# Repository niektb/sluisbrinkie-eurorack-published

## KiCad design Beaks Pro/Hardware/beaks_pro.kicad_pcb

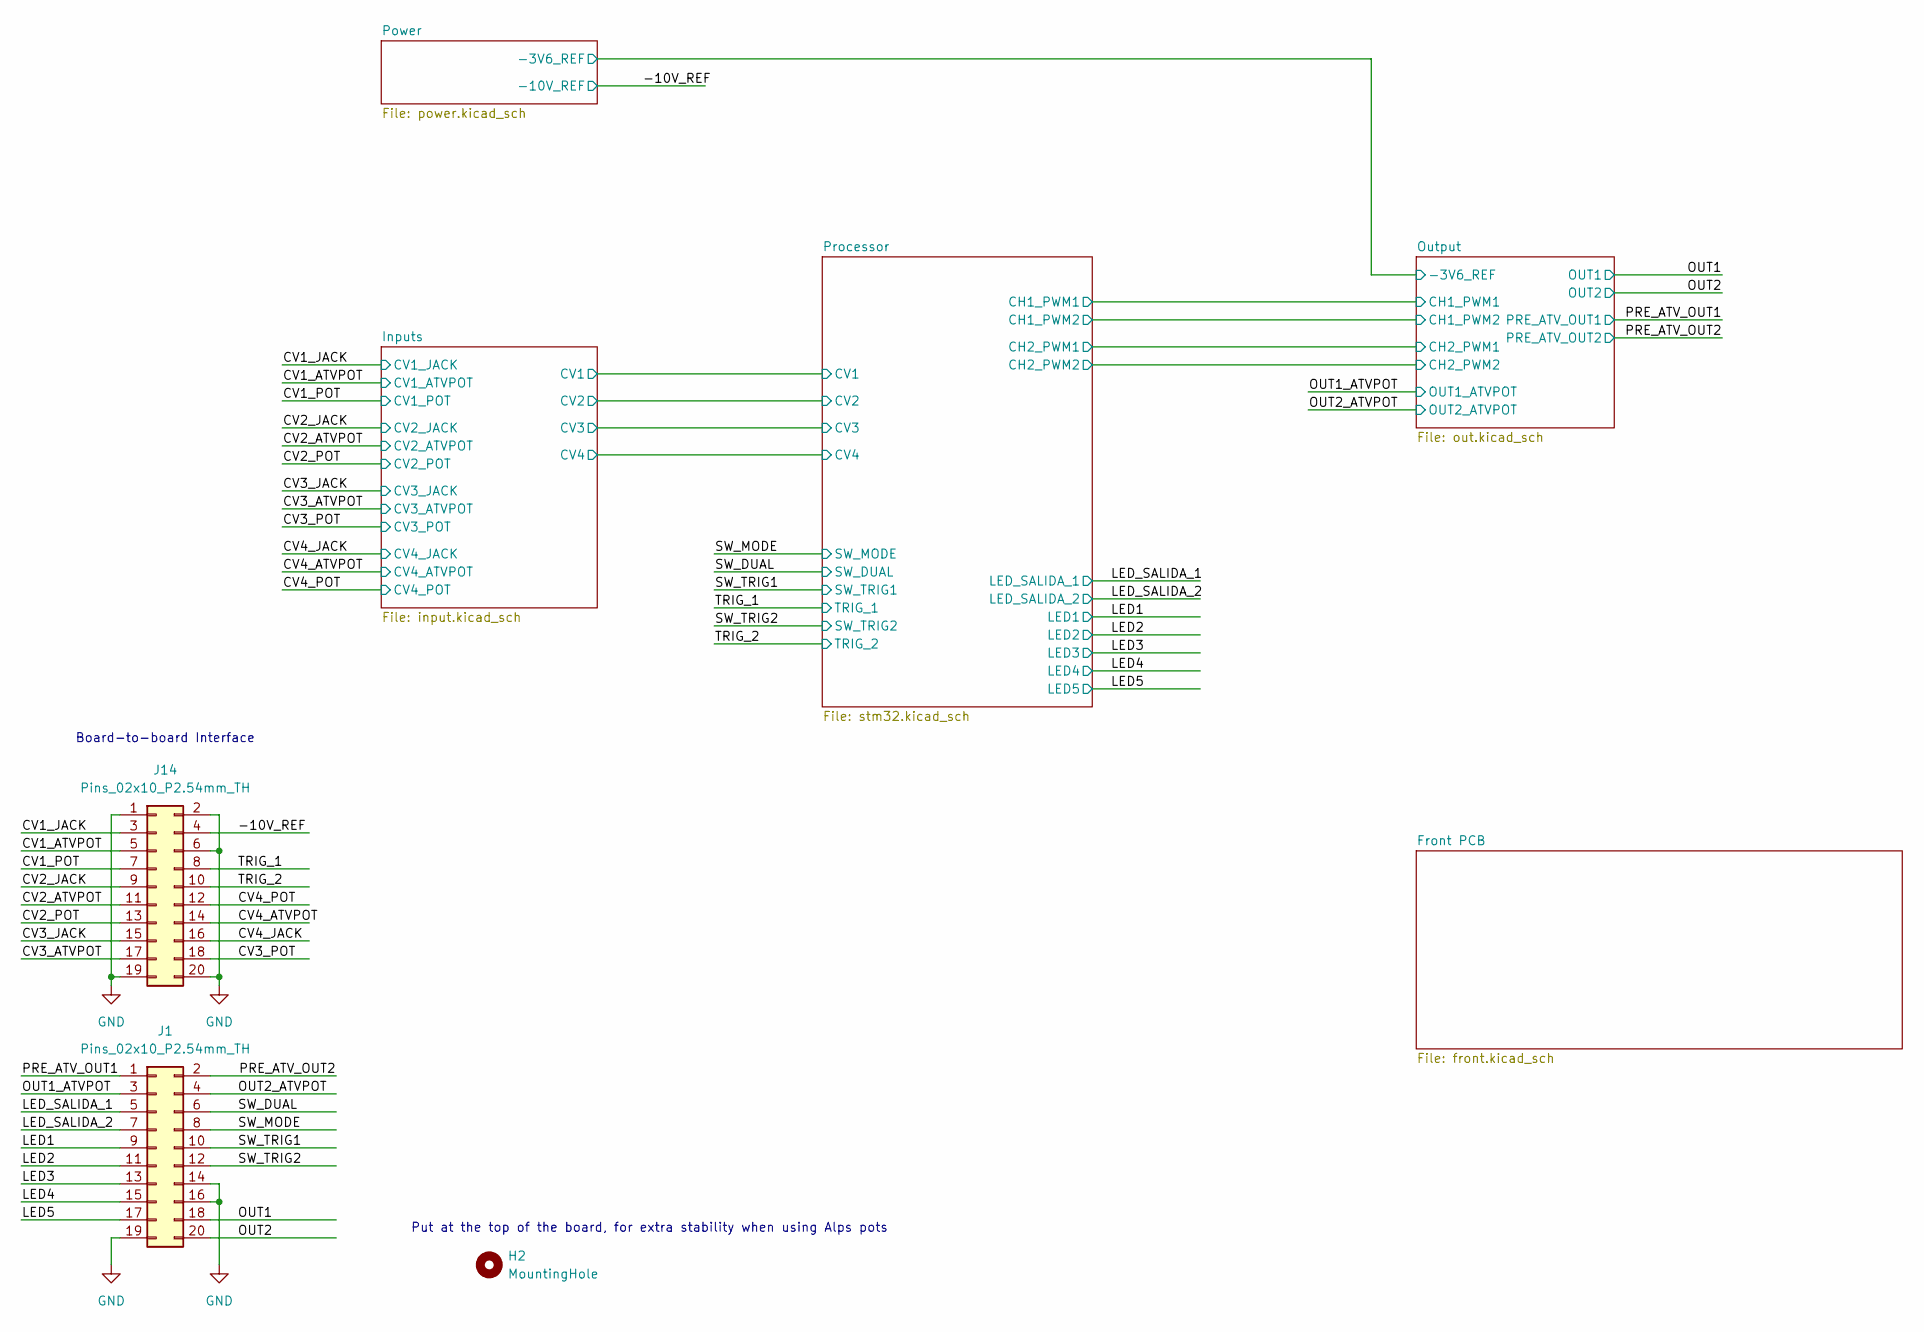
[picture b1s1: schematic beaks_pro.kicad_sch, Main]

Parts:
H2: MountingHole; MountingHole_2.7mm_M2.5
J1, J14: Pins_02x10_P2.54mm_TH; PinHeader_2x10_P2.54mm_Vertical

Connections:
/CV1_ATVPOT: J14.5; also elsewhere on the board
/CV1_JACK: J14.3; also elsewhere on the board
/CV1_POT: J14.7; also elsewhere on the board
/CV2_ATVPOT: J14.11; also elsewhere on the board
/CV2_JACK: J14.9; also elsewhere on the board
/CV2_POT: J14.13; also elsewhere on the board
/CV3_ATVPOT: J14.17; also elsewhere on the board
/CV3_JACK: J14.15; also elsewhere on the board
/CV3_POT: J14.18; also elsewhere on the board
/CV4_ATVPOT: J14.14; also elsewhere on the board
/CV4_JACK: J14.16; also elsewhere on the board
/CV4_POT: J14.12; also elsewhere on the board
/LED1: J1.9; also elsewhere on the board
/LED2: J1.11; also elsewhere on the board
/LED3: J1.13; also elsewhere on the board
/LED4: J1.15; also elsewhere on the board
/LED5: J1.17; also elsewhere on the board
/LED_SALIDA_1: J1.5; also elsewhere on the board
/LED_SALIDA_2: J1.7; also elsewhere on the board
/OUT1: J1.18; also elsewhere on the board
/OUT1_ATVPOT: J1.3; also elsewhere on the board
/OUT2: J1.20; also elsewhere on the board
/OUT2_ATVPOT: J1.4; also elsewhere on the board
/PRE_ATV_OUT1: J1.1; also elsewhere on the board
/PRE_ATV_OUT2: J1.2; also elsewhere on the board
/SW_DUAL: J1.6; also elsewhere on the board
/SW_MODE: J1.8; also elsewhere on the board
/SW_TRIG1: J1.10; also elsewhere on the board
/SW_TRIG2: J1.12; also elsewhere on the board
/TRIG_1: J14.8; also elsewhere on the board
/TRIG_2: J14.10; also elsewhere on the board

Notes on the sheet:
Put at the top of the board, for extra stability when using Alps pots
Board-to-board Interface

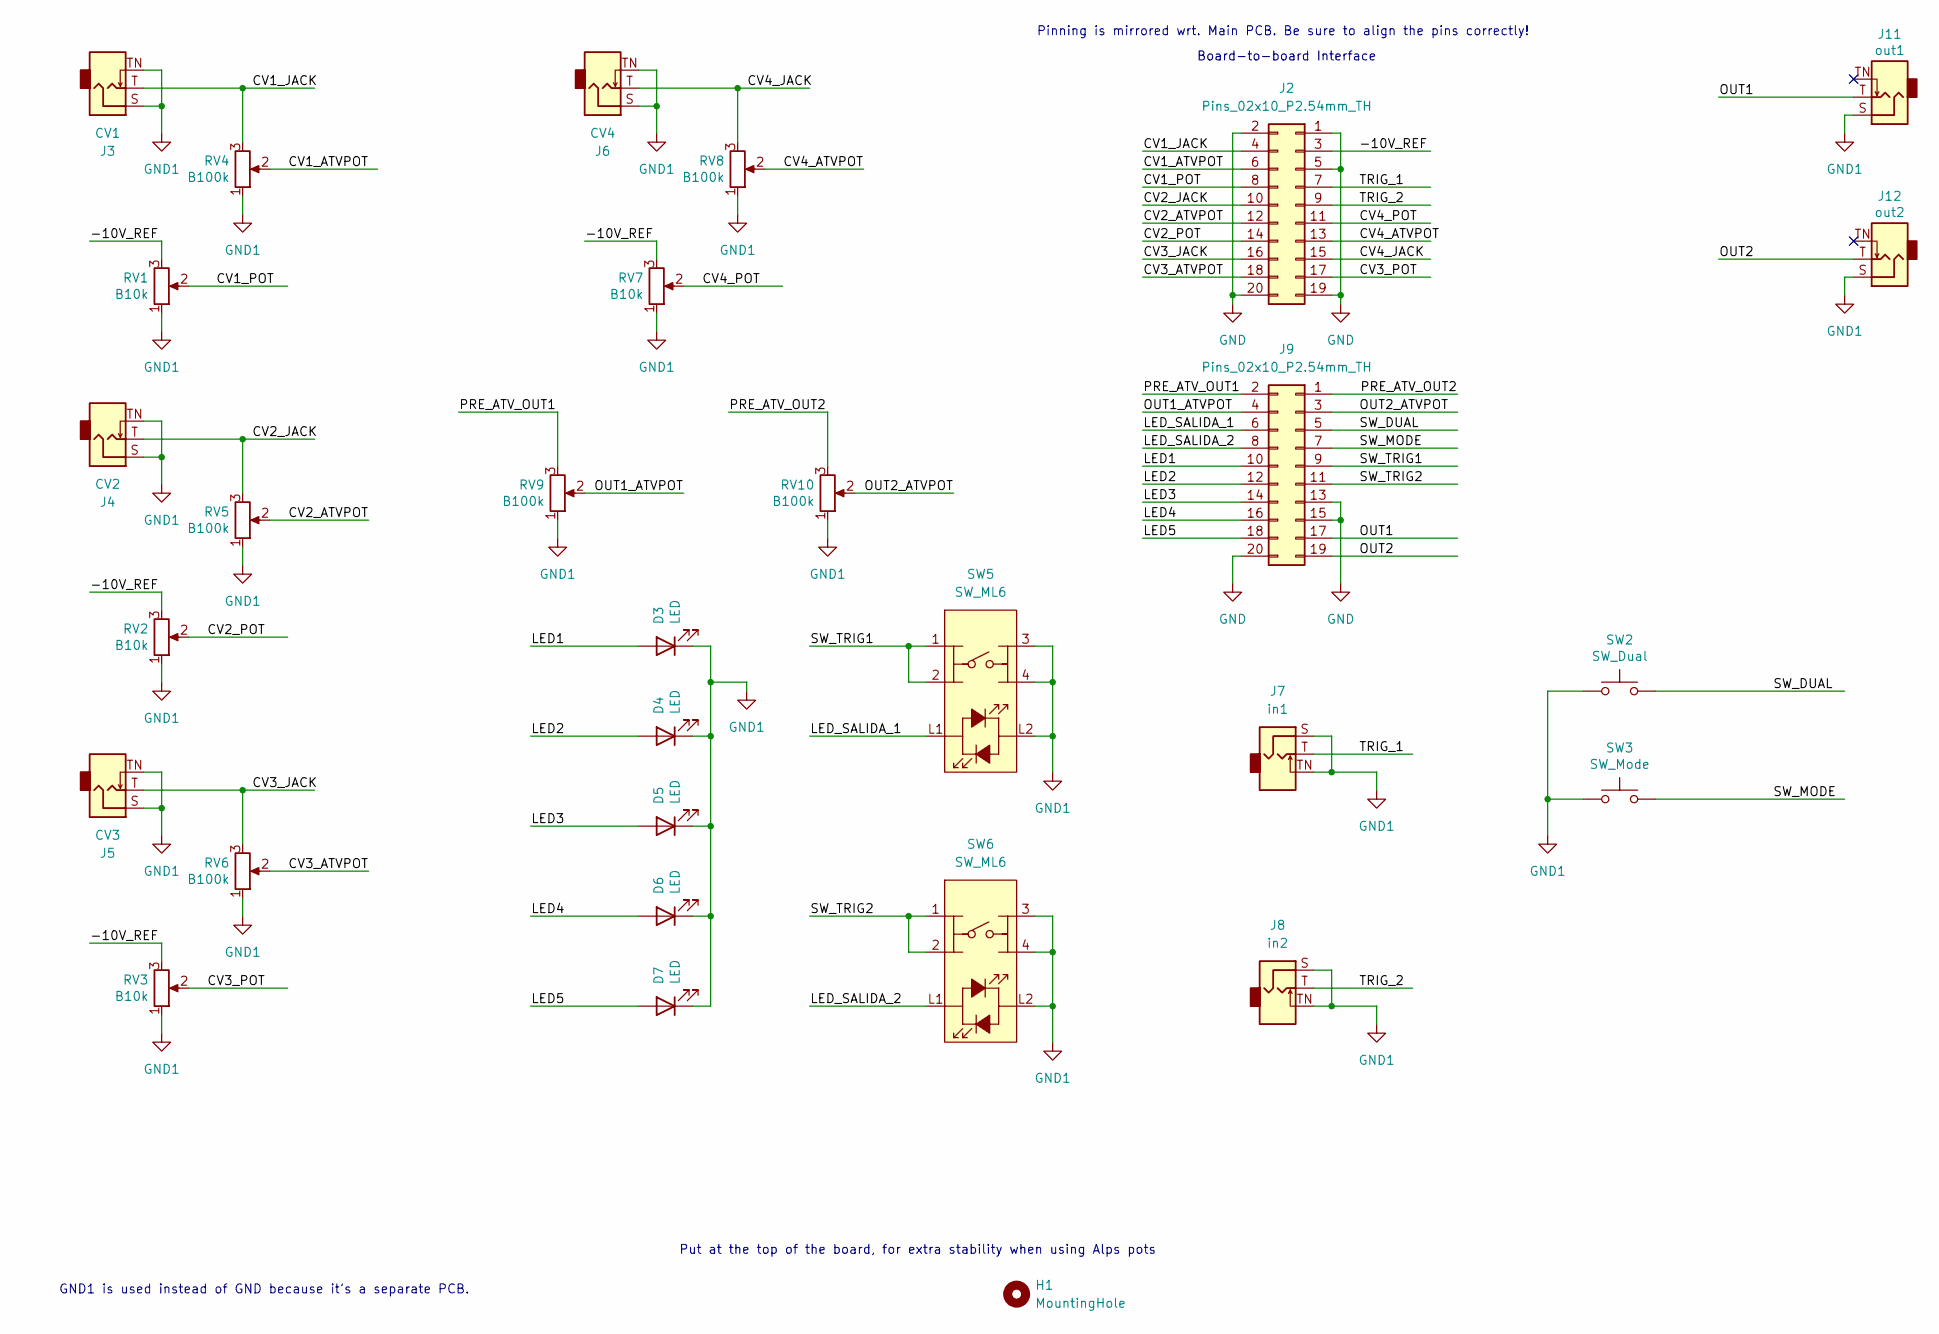
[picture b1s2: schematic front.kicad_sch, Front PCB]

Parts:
D3, D4, D5, D6, D7: LED; LED_D3.0mm
H1: MountingHole; MountingHole_2.7mm_M2.5
J2, J9: Pins_02x10_P2.54mm_TH; PinSocket_2x10_P2.54mm_Vertical
J3: CV1; Jack_3.5mm_QingPu_WQP-PJ398SM_Vertical_CircularHoles_3D
J4: CV2; Jack_3.5mm_QingPu_WQP-PJ398SM_Vertical_CircularHoles_3D
J5: CV3; Jack_3.5mm_QingPu_WQP-PJ398SM_Vertical_CircularHoles_3D
J6: CV4; Jack_3.5mm_QingPu_WQP-PJ398SM_Vertical_CircularHoles_3D
J7: in1; Jack_3.5mm_QingPu_WQP-PJ398SM_Vertical_CircularHoles_3D
J8: in2; Jack_3.5mm_QingPu_WQP-PJ398SM_Vertical_CircularHoles_3D
J11: out1; Jack_3.5mm_QingPu_WQP-PJ398SM_Vertical_CircularHoles_3D
J12: out2; Jack_3.5mm_QingPu_WQP-PJ398SM_Vertical_CircularHoles_3D
RV1, RV2, RV3, RV7: B10k; Potentiometer_Alps_RK09K_Single_Vertical_DSHAFT
RV4, RV5, RV6, RV8, RV9, RV10: B100k; Potentiometer_Alps_RK09K_Single_Vertical
SW2: SW_Dual; SW_PUSH_6mm_H13mm
SW3: SW_Mode; SW_PUSH_6mm_H13mm
SW5, SW6: SW_ML6; ML6-H2T2GQA

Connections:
/Front PCB/-10V_REF: J2.3, RV1.3, RV2.3, RV3.3, RV7.3
/Front PCB/CV1_ATVPOT: J2.6, RV4.2
/Front PCB/CV1_JACK: J2.4, J3.T, RV4.3
/Front PCB/CV1_POT: J2.8, RV1.2
/Front PCB/CV2_ATVPOT: J2.12, RV5.2
/Front PCB/CV2_JACK: J2.10, J4.T, RV5.3
/Front PCB/CV2_POT: J2.14, RV2.2
/Front PCB/CV3_ATVPOT: J2.18, RV6.2
/Front PCB/CV3_JACK: J2.16, J5.T, RV6.3
/Front PCB/CV3_POT: J2.17, RV3.2
/Front PCB/CV4_ATVPOT: J2.13, RV8.2
/Front PCB/CV4_JACK: J2.15, J6.T, RV8.3
/Front PCB/CV4_POT: J2.11, RV7.2
/Front PCB/LED1: D3.2 (A), J9.10
/Front PCB/LED2: D4.2 (A), J9.12
/Front PCB/LED3: D5.2 (A), J9.14
/Front PCB/LED4: D6.2 (A), J9.16
/Front PCB/LED5: D7.2 (A), J9.18
/Front PCB/LED_SALIDA_1: J9.6, SW5.L1
/Front PCB/LED_SALIDA_2: J9.8, SW6.L1
/Front PCB/OUT1: J9.17, J11.T
/Front PCB/OUT1_ATVPOT: J9.4, RV9.2
/Front PCB/OUT2: J9.19, J12.T
/Front PCB/OUT2_ATVPOT: J9.3, RV10.2
/Front PCB/PRE_ATV_OUT1: J9.2, RV9.3
/Front PCB/PRE_ATV_OUT2: J9.1, RV10.3
/Front PCB/SW_DUAL: J9.5, SW2.1
/Front PCB/SW_MODE: J9.7, SW3.1
/Front PCB/SW_TRIG1: J9.9, SW5.1, SW5.2
/Front PCB/SW_TRIG2: J9.11, SW6.1, SW6.2
/Front PCB/TRIG_1: J2.7, J7.T
/Front PCB/TRIG_2: J2.9, J8.T
GND1: D3.1 (K), D4.1 (K), D5.1 (K), D6.1 (K), D7.1 (K), J3.S, J3.TN, J4.S, J4.TN, J5.S, J5.TN, J6.S, J6.TN, J7.S, J7.TN, J8.S, J8.TN, J11.S, J12.S, RV1.1, RV2.1, RV3.1, RV4.1, RV5.1, RV6.1, RV7.1, RV8.1, RV9.1, RV10.1, SW2.2, SW3.2, SW5.3, SW5.4 (A), SW5.L2, SW6.3, SW6.4 (A), SW6.L2

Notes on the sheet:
Pinning is mirrored wrt. Main PCB. Be sure to align the pins correctly!
Board-to-board Interface
Put at the top of the board, for extra stability when using Alps pots
GND1 is used instead of GND because it's a separate PCB.

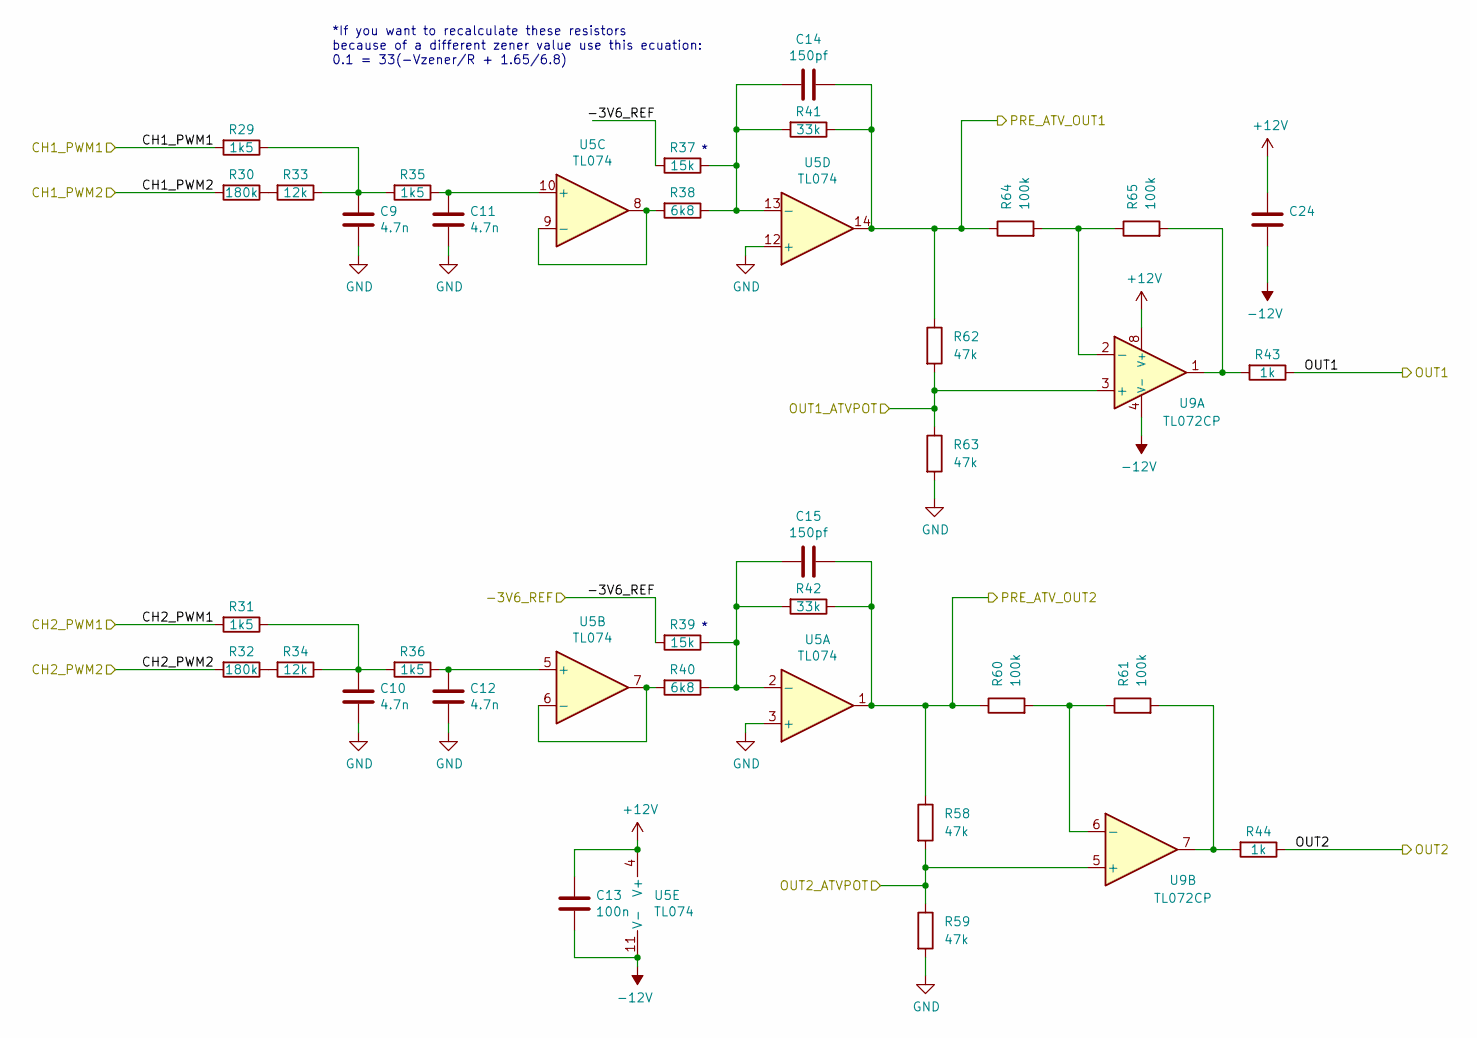
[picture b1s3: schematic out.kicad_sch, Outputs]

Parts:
C9, C10, C11, C12: 4.7n; C_Disc_D3.4mm_W2.1mm_P2.50mm
C13, C24: 100n; C_Rect_L10.0mm_W4.0mm_P7.50mm_MKS4
C14, C15: 150pf; C_Disc_D3.4mm_W2.1mm_P2.50mm
R29, R31, R35, R36: 1k5; R_Axial_DIN0207_L6.3mm_D2.5mm_P7.62mm_Horizontal
R30, R32: 180k; R_Axial_DIN0207_L6.3mm_D2.5mm_P7.62mm_Horizontal
R33, R34: 12k; R_Axial_DIN0207_L6.3mm_D2.5mm_P7.62mm_Horizontal
R37, R39: 15k; R_Axial_DIN0207_L6.3mm_D2.5mm_P7.62mm_Horizontal
R38, R40: 6k8; R_Axial_DIN0207_L6.3mm_D2.5mm_P7.62mm_Horizontal
R41, R42: 33k; R_Axial_DIN0207_L6.3mm_D2.5mm_P7.62mm_Horizontal
R43, R44: 1k; R_Axial_DIN0207_L6.3mm_D2.5mm_P7.62mm_Horizontal
R58, R59, R62, R63: 47k; R_Axial_DIN0207_L6.3mm_D2.5mm_P7.62mm_Horizontal
R60, R61, R64, R65: 100k; R_Axial_DIN0207_L6.3mm_D2.5mm_P7.62mm_Horizontal
U5: TL074; DIP-14_W7.62mm_Socket_LongPads
U9: TL072CP; DIP-8_W7.62mm_Socket_LongPads

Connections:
-12V: C13.2, C24.2, U5.11 (V-), U9.4 (V-); also elsewhere on the board
/OUT1: R43.1; also elsewhere on the board
/OUT1_ATVPOT: R62.2, R63.1, U9.3 (+); also elsewhere on the board
/OUT2: R44.1; also elsewhere on the board
/OUT2_ATVPOT: R58.2, R59.1, U9.5 (+); also elsewhere on the board
/Output/-3V6_REF: R37.2, R39.2; also elsewhere on the board
/Output/CH1_PWM1: R29.2; also elsewhere on the board
/Output/CH1_PWM2: R30.2; also elsewhere on the board
/Output/CH2_PWM1: R31.2; also elsewhere on the board
/Output/CH2_PWM2: R32.2; also elsewhere on the board
/PRE_ATV_OUT1: C14.2, R41.1, R62.1, R64.1, U5.14; also elsewhere on the board
/PRE_ATV_OUT2: C15.2, R42.1, R58.1, R60.1, U5.1; also elsewhere on the board
unnamed: C9.1, R29.1, R33.1, R35.2
unnamed: C10.1, R31.1, R34.1, R36.2
unnamed: R30.1, R33.2
unnamed: R32.1, R34.2
unnamed: R43.2, R65.2, U9.1
unnamed: R44.2, R61.2, U9.7
unnamed: C15.1, R39.1, R40.1, R42.2, U5.2 (-)
unnamed: C12.1, R36.1, U5.5 (+)
unnamed: R40.2, U5.6 (-), U5.7
unnamed: C11.1, R35.1, U5.10 (+)
unnamed: R38.2, U5.8, U5.9 (-)
unnamed: C14.1, R37.1, R38.1, R41.2, U5.13 (-)
unnamed: R64.2, R65.1, U9.2 (-)
unnamed: R60.2, R61.1, U9.6 (-)

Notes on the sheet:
*If you want to recalculate these resistors because of a different zener value use this ecuation: 0.1 = 33(-Vzener/R + 1.65/6.8)

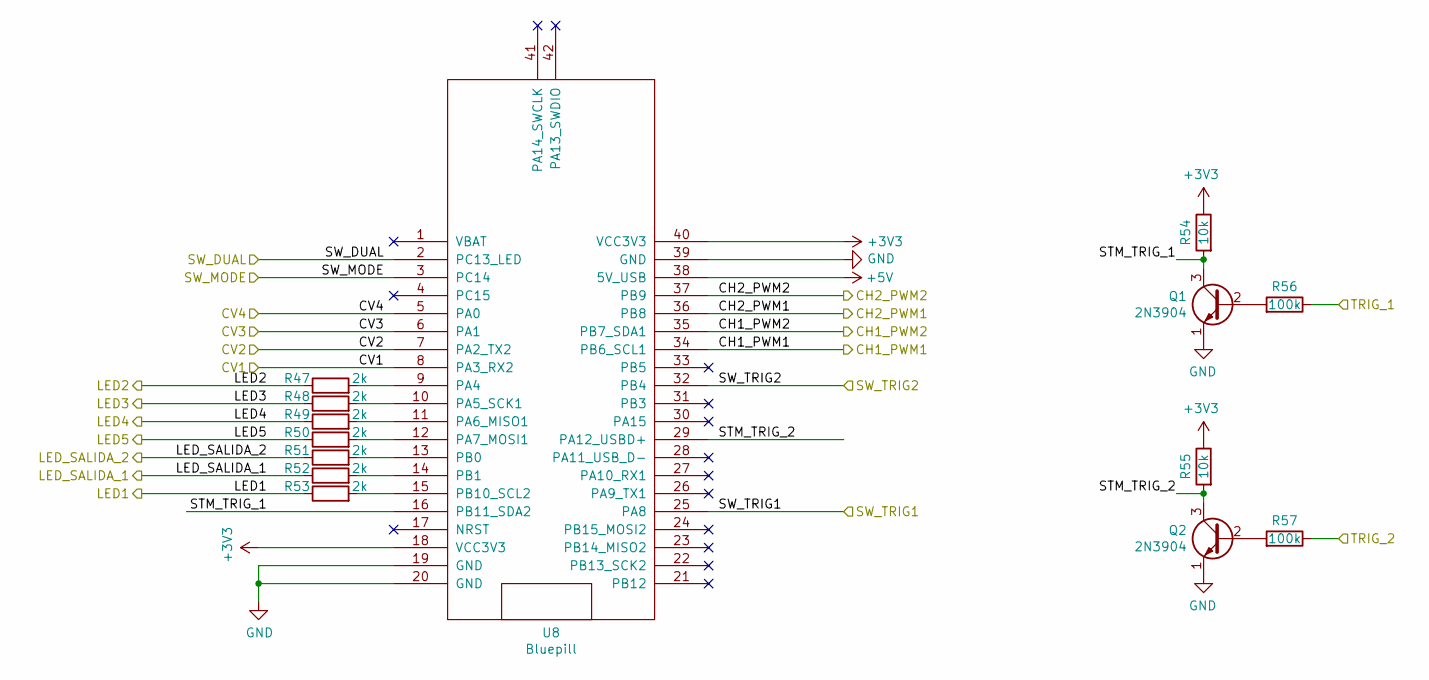
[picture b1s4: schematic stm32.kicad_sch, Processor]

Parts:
Q1, Q2: 2N3904; TO-92_Inline_Wide
R47, R48, R49, R50, R51, R52, R53: 2k; R_Axial_DIN0207_L6.3mm_D2.5mm_P7.62mm_Horizontal
R54, R55: 10k; R_Axial_DIN0207_L6.3mm_D2.5mm_P7.62mm_Horizontal
R56, R57: 100k; R_Axial_DIN0207_L6.3mm_D2.5mm_P7.62mm_Horizontal
U8: Bluepill; BluePill_STM32F103C

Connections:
+3V3: R54.1, R55.1, U8.18 (VCC3V3), U8.40 (VCC3V3); also elsewhere on the board
/Inputs/CV1: U8.8 (PA3_RX2); also elsewhere on the board
/Inputs/CV2: U8.7 (PA2_TX2); also elsewhere on the board
/Inputs/CV3: U8.6 (PA1); also elsewhere on the board
/Inputs/CV4: U8.5 (PA0); also elsewhere on the board
/LED1: R53.1; also elsewhere on the board
/LED2: R47.1; also elsewhere on the board
/LED3: R48.1; also elsewhere on the board
/LED4: R49.1; also elsewhere on the board
/LED5: R50.1; also elsewhere on the board
/LED_SALIDA_1: R52.1; also elsewhere on the board
/LED_SALIDA_2: R51.1; also elsewhere on the board
/Output/CH1_PWM1: U8.34 (PB6_SCL1); also elsewhere on the board
/Output/CH1_PWM2: U8.35 (PB7_SDA1); also elsewhere on the board
/Output/CH2_PWM1: U8.36 (PB8); also elsewhere on the board
/Output/CH2_PWM2: U8.37 (PB9); also elsewhere on the board
/Processor/STM_TRIG_1: Q1.3 (C), R54.2, U8.16 (PB11_SDA2)
/Processor/STM_TRIG_2: Q2.3 (C), R55.2, U8.29 (PA12_USBD+)
/SW_DUAL: U8.2 (PC13_LED); also elsewhere on the board
/SW_MODE: U8.3 (PC14); also elsewhere on the board
/SW_TRIG1: U8.25 (PA8); also elsewhere on the board
/SW_TRIG2: U8.32 (PB4); also elsewhere on the board
/TRIG_1: R56.1; also elsewhere on the board
/TRIG_2: R57.1; also elsewhere on the board
unnamed: Q1.2 (B), R56.2
unnamed: Q2.2 (B), R57.2
unnamed: R47.2, U8.9 (PA4)
unnamed: R48.2, U8.10 (PA5_SCK1)
unnamed: R49.2, U8.11 (PA6_MISO1)
unnamed: R50.2, U8.12 (PA7_MOSI1)
unnamed: R51.2, U8.13 (PB0)
unnamed: R52.2, U8.14 (PB1)
unnamed: R53.2, U8.15 (PB10_SCL2)

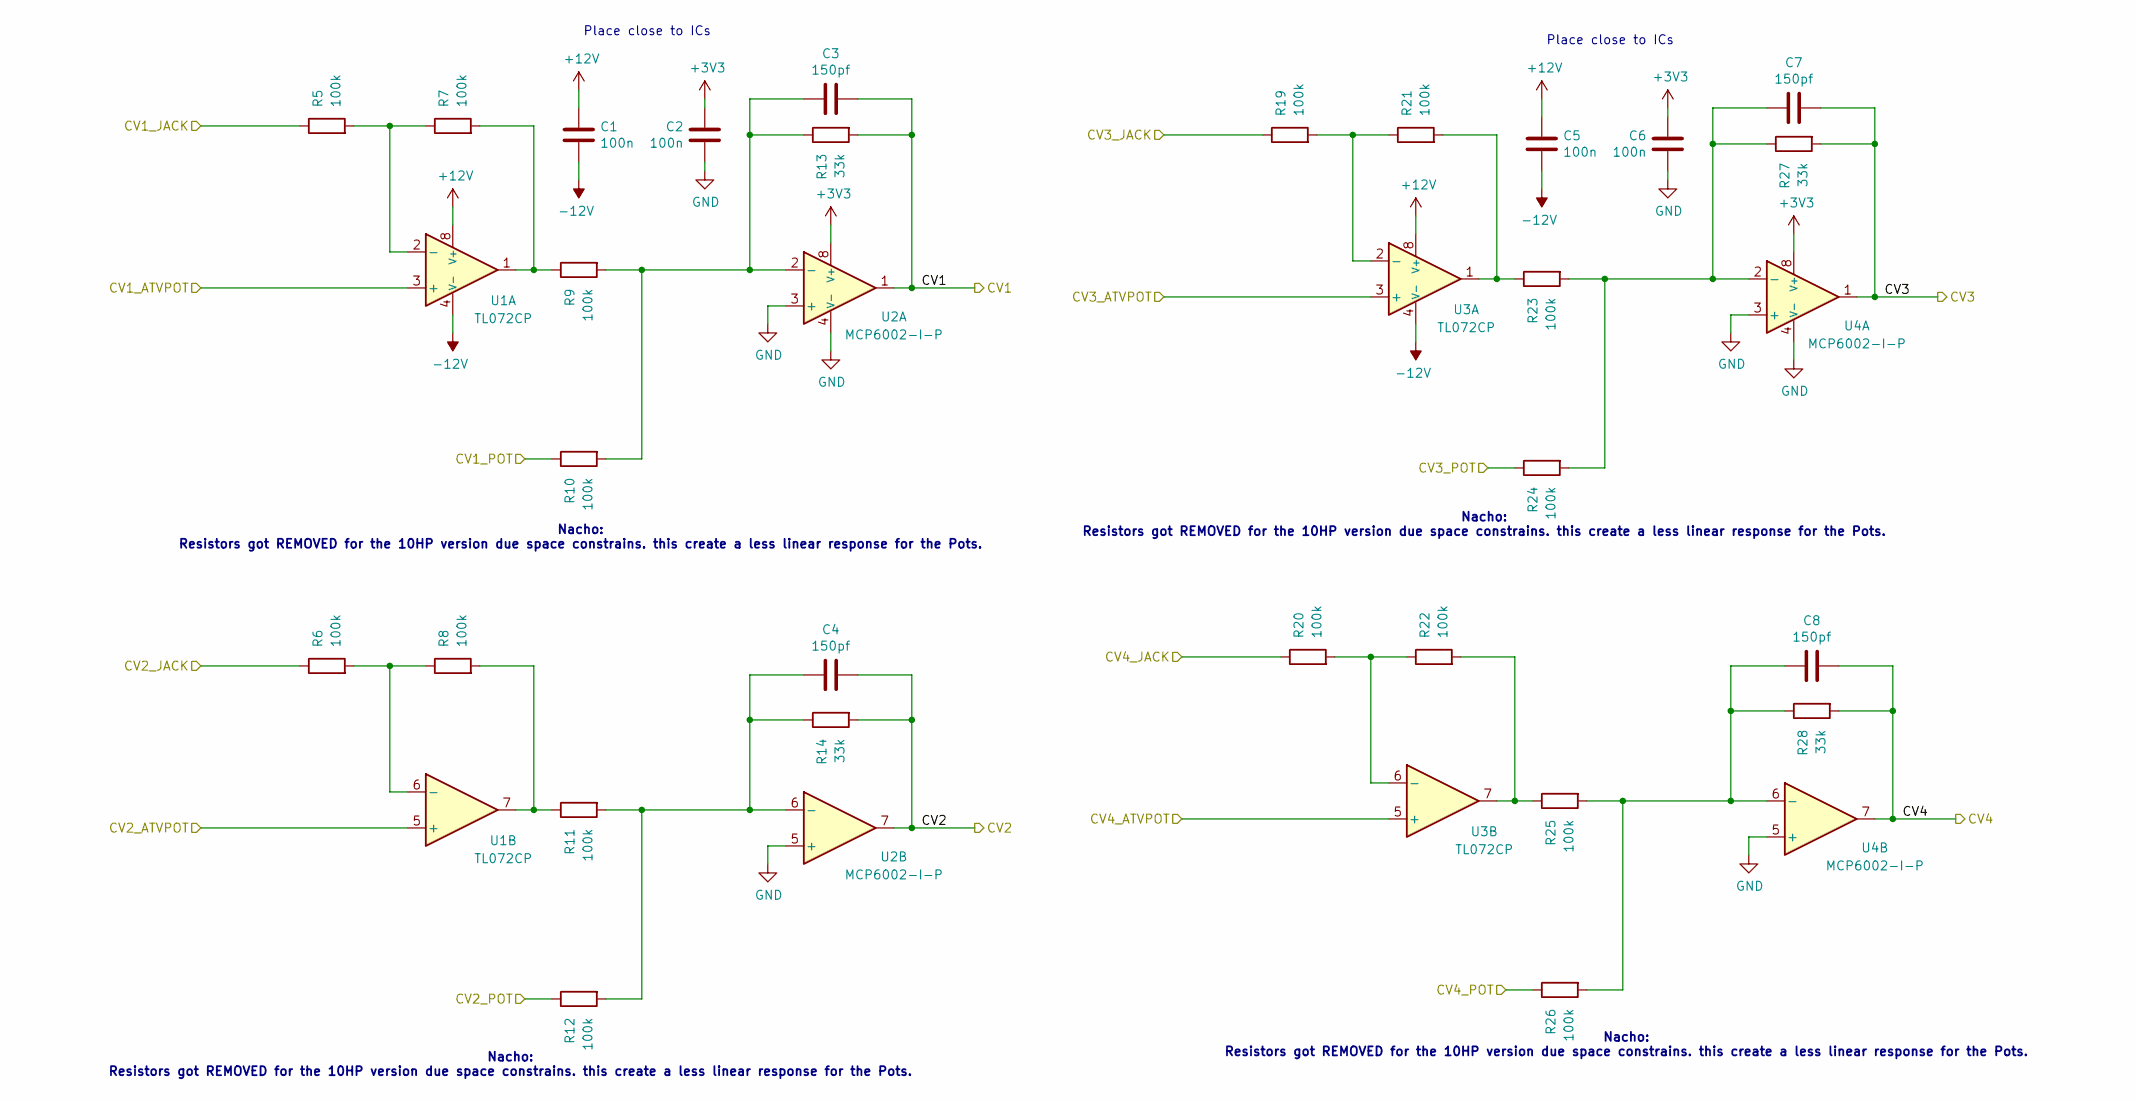
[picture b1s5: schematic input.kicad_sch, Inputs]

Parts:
C1, C2, C5, C6: 100n; C_Rect_L10.0mm_W4.0mm_P7.50mm_MKS4
C3, C4, C7, C8: 150pf; C_Disc_D3.4mm_W2.1mm_P2.50mm
R5, R6, R7, R8, R9, R10, R11, R12, R19, R20, R21, R22, R23, R24, R25, R26: 100k; R_Axial_DIN0207_L6.3mm_D2.5mm_P7.62mm_Horizontal
R13, R14, R27, R28: 33k; R_Axial_DIN0207_L6.3mm_D2.5mm_P7.62mm_Horizontal
U1, U3: TL072CP; CERDIP-8_W7.62mm_SideBrazed_LongPads_Socket
U2, U4: MCP6002-I-P; CERDIP-8_W7.62mm_SideBrazed_LongPads_Socket

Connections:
+3V3: C2.1, C6.1, U2.8 (V+), U4.8 (V+); also elsewhere on the board
-12V: C1.2, C5.2, U1.4 (V-), U3.4 (V-); also elsewhere on the board
/CV1_ATVPOT: U1.3 (+); also elsewhere on the board
/CV1_JACK: R5.1; also elsewhere on the board
/CV1_POT: R10.1; also elsewhere on the board
/CV2_ATVPOT: U1.5 (+); also elsewhere on the board
/CV2_JACK: R6.1; also elsewhere on the board
/CV2_POT: R12.1; also elsewhere on the board
/CV3_ATVPOT: U3.3 (+); also elsewhere on the board
/CV3_JACK: R19.1; also elsewhere on the board
/CV3_POT: R24.1; also elsewhere on the board
/CV4_ATVPOT: U3.5 (+); also elsewhere on the board
/CV4_JACK: R20.1; also elsewhere on the board
/CV4_POT: R26.1; also elsewhere on the board
/Inputs/CV1: C3.2, R13.2, U2.1; also elsewhere on the board
/Inputs/CV2: C4.2, R14.2, U2.7; also elsewhere on the board
/Inputs/CV3: C7.2, R27.2, U4.1; also elsewhere on the board
/Inputs/CV4: C8.2, R28.2, U4.7; also elsewhere on the board
unnamed: R7.2, R9.1, U1.1
unnamed: R8.2, R11.1, U1.7
unnamed: R21.2, R23.1, U3.1
unnamed: R22.2, R25.1, U3.7
unnamed: R5.2, R7.1, U1.2 (-)
unnamed: R6.2, R8.1, U1.6 (-)
unnamed: C3.1, R9.2, R10.2, R13.1, U2.2 (-)
unnamed: C4.1, R11.2, R12.2, R14.1, U2.6 (-)
unnamed: R19.2, R21.1, U3.2 (-)
unnamed: R20.2, R22.1, U3.6 (-)
unnamed: C7.1, R23.2, R24.2, R27.1, U4.2 (-)
unnamed: C8.1, R25.2, R26.2, R28.1, U4.6 (-)

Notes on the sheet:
Nacho: Resistors got REMOVED for the 10HP version due space constrains. this create a less linear response for the Pots.
Place close to ICs

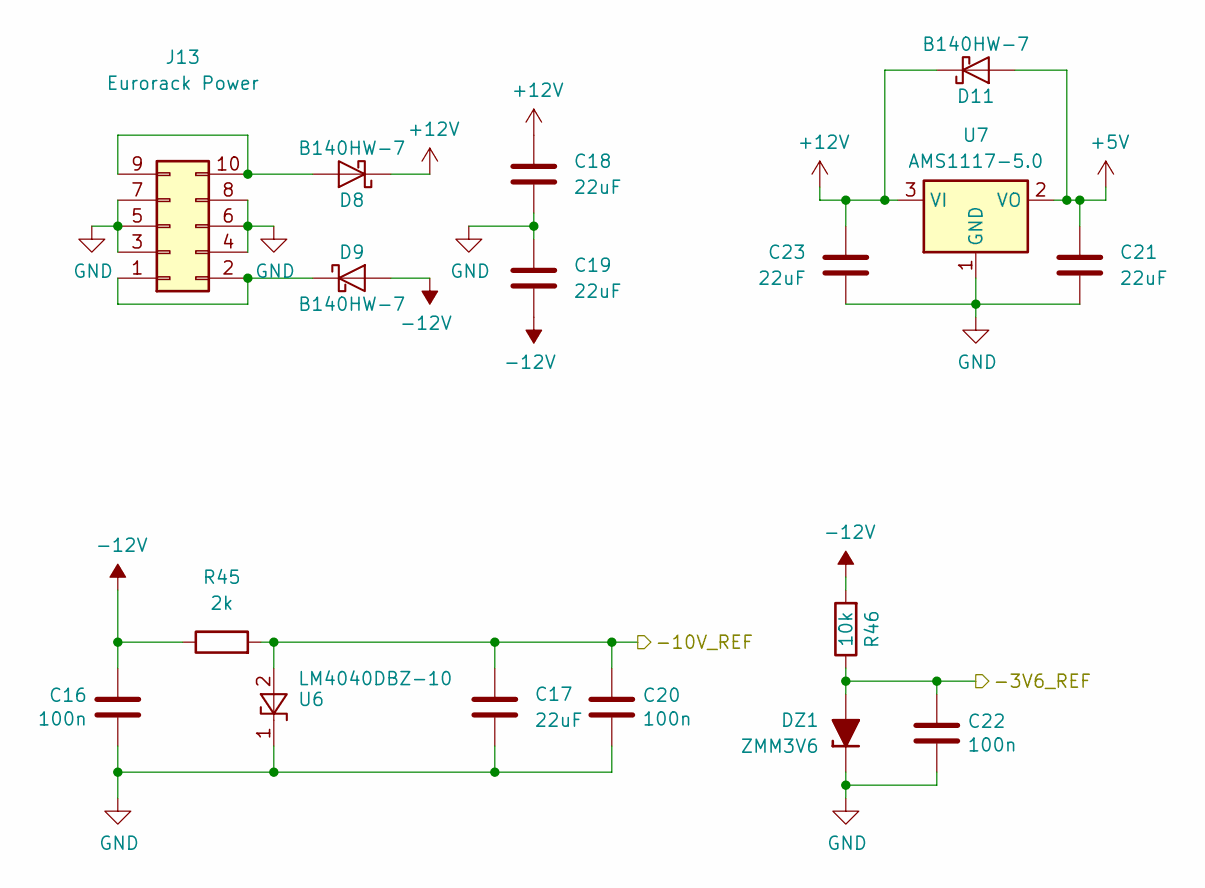
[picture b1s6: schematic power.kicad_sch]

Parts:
C16, C20, C22: 100n; C_0603_1608Metric_Pad1.08x0.95mm_HandSolder
C17, C18, C19, C21, C23: 22uF; C_1206_3216Metric_Pad1.33x1.80mm_HandSolder
D8, D9, D11: B140HW-7; D_SOD-123; Part Number B140HW-7; JLCPCB ID C134429
DZ1: ZMM3V6; D_SOD-323
J13: Eurorack Power; IDC-Header_2x05_P2.54mm_Vertical
R45: 2k; R_0603_1608Metric_Pad0.98x0.95mm_HandSolder
R46: 10k; R_0603_1608Metric_Pad0.98x0.95mm_HandSolder
U6: LM4040DBZ-10; SOT-23
U7: AMS1117-5.0; SOT-223-3_TabPin2

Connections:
-12V: C16.1, C19.2, D9.2 (A), R45.1, R46.2; also elsewhere on the board
/Output/-3V6_REF: C22.1, DZ1.2 (A), R46.1; also elsewhere on the board
unnamed: D8.2 (A), J13.9, J13.10
unnamed: D9.1 (K), J13.1, J13.2

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
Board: 2 copper layers, 138 parts (2 on the bottom side), 118 nets, no tracks yet.

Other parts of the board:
D10: 3.6; D_DO-35_SOD27_P7.62mm_Horizontal
R1, R2, R3, R4, R15, R16, R17, R18: 47k; R_Axial_DIN0207_L6.3mm_D2.5mm_P7.62mm_Horizontal

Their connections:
/CV1_ATVPOT: R1.2, R2.1; also elsewhere on the board
/CV1_JACK: R1.1; also elsewhere on the board
/CV2_ATVPOT: R3.2, R4.1; also elsewhere on the board
/CV2_JACK: R3.1; also elsewhere on the board
/CV3_ATVPOT: R15.2, R16.1; also elsewhere on the board
/CV3_JACK: R15.1; also elsewhere on the board
/CV4_ATVPOT: R17.2, R18.1; also elsewhere on the board
/CV4_JACK: R17.1; also elsewhere on the board
/Output/-3V6_REF: D10.2 (A); also elsewhere on the board

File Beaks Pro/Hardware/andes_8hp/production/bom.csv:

Designator,Footprint,Quantity,Value,LCSC Part #
"C1, C13, C16, C2, C20, C22, C24, C25, C26, C5, C6",0603,11,100n,
"C10, C11, C12, C9",0603,4,4.7n,
"C14, C15, C3, C4, C7, C8",0603,6,150pf,
"C17, C18, C19, C21, C23",1206,5,22uF,
"D11, D8, D9",D_SOD-123,3,B140HW-7,
DZ1,D_SOD-323,1,ZMM3V6,
J1,PinSocket_2x08_P2.54mm_Vertical,1,Conn_02x08_Odd_Even,
J13,IDC-Header_2x05_P2.54mm_Vertical,1,Eurorack Power,
J14,PinSocket_2x12_P2.54mm_Vertical,1,Conn_02x12_Odd_Even,
"Q1, Q2",SOT-23,2,S8050 J3Y,
"R1, R15, R16, R17, R18, R2, R3, R4, R58, R59, R62, R63",0603,12,47k,
"R10, R11, R12, R19, R20, R21, R22, R23, R24, R25, R26, R5, R56, R57, R6, R60, R61, R64, R65, R7, R8, R9",0603,22,100k,
"R13, R14, R27, R28, R41, R42",0603,6,33k,
"R29, R31, R35, R36",0603,4,1k5,
"R30, R32",0603,2,180k,
"R33, R34",0603,2,12k,
"R37, R39",0603,2,15k,
"R38, R40",0603,2,6k8,
"R43, R44",0603,2,1k,
"R45, R47, R48, R49, R50, R51, R52, R53",0603,8,2k,
"R46, R54, R55",0603,3,10k,
"U1, U3, U9",SO-8_3.9x4.9mm_P1.27mm,3,TL072CD,
"U2, U4",SO-8_3.9x4.9mm_P1.27mm,2,MCP6002-I-SN,
U5,SOIC-14_3.9x8.7mm_P1.27mm,1,TL074CD,
U6,SOT-23,1,LM4040DBZ-10,
U7,SOT-223-3_TabPin2,1,AMS1117-5.0,
U8,BluePill_STM32F103C,1,Bluepill,
